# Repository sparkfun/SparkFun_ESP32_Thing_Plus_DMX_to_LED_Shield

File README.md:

SparkFun ESP32 Thing Plus DMX to LED Shield
========================================

[*SparkFun ESP32 DMX to LED Shield(DEV-15110)*](https://www.sparkfun.com/products/15110)

The SparkFun ESP32 DMX to LED Shield is capable of DMX output, input, as well as Artnet input. The shield is electrically isolated to keep with DMX spec. This library has been written to control DMX output and input.

Repository Contents
-------------------

* **/Hardware** - Eagle design files (.brd, .sch)
* **/Production** - Production panel files (.brd)

Documentation
--------------
* **[Hookup Guide](https://learn.sparkfun.com/tutorials/sparkfun-esp32-dmx-to-led-shield)** - Basic hookup guide for the [SparkFun ESP32 DMX to LED Shield](https://www.sparkfun.com/products/15110).

License Information
-------------------

This product is _**open source**_! 

Please review the LICENSE.md file for license information.

If you have any questions or concerns on licensing, please visit the [SparkFun Forum](https://forum.sparkfun.com/index.php) and post a topic.

Distributed as-is; no warranty is given.

- Your friends at SparkFun.

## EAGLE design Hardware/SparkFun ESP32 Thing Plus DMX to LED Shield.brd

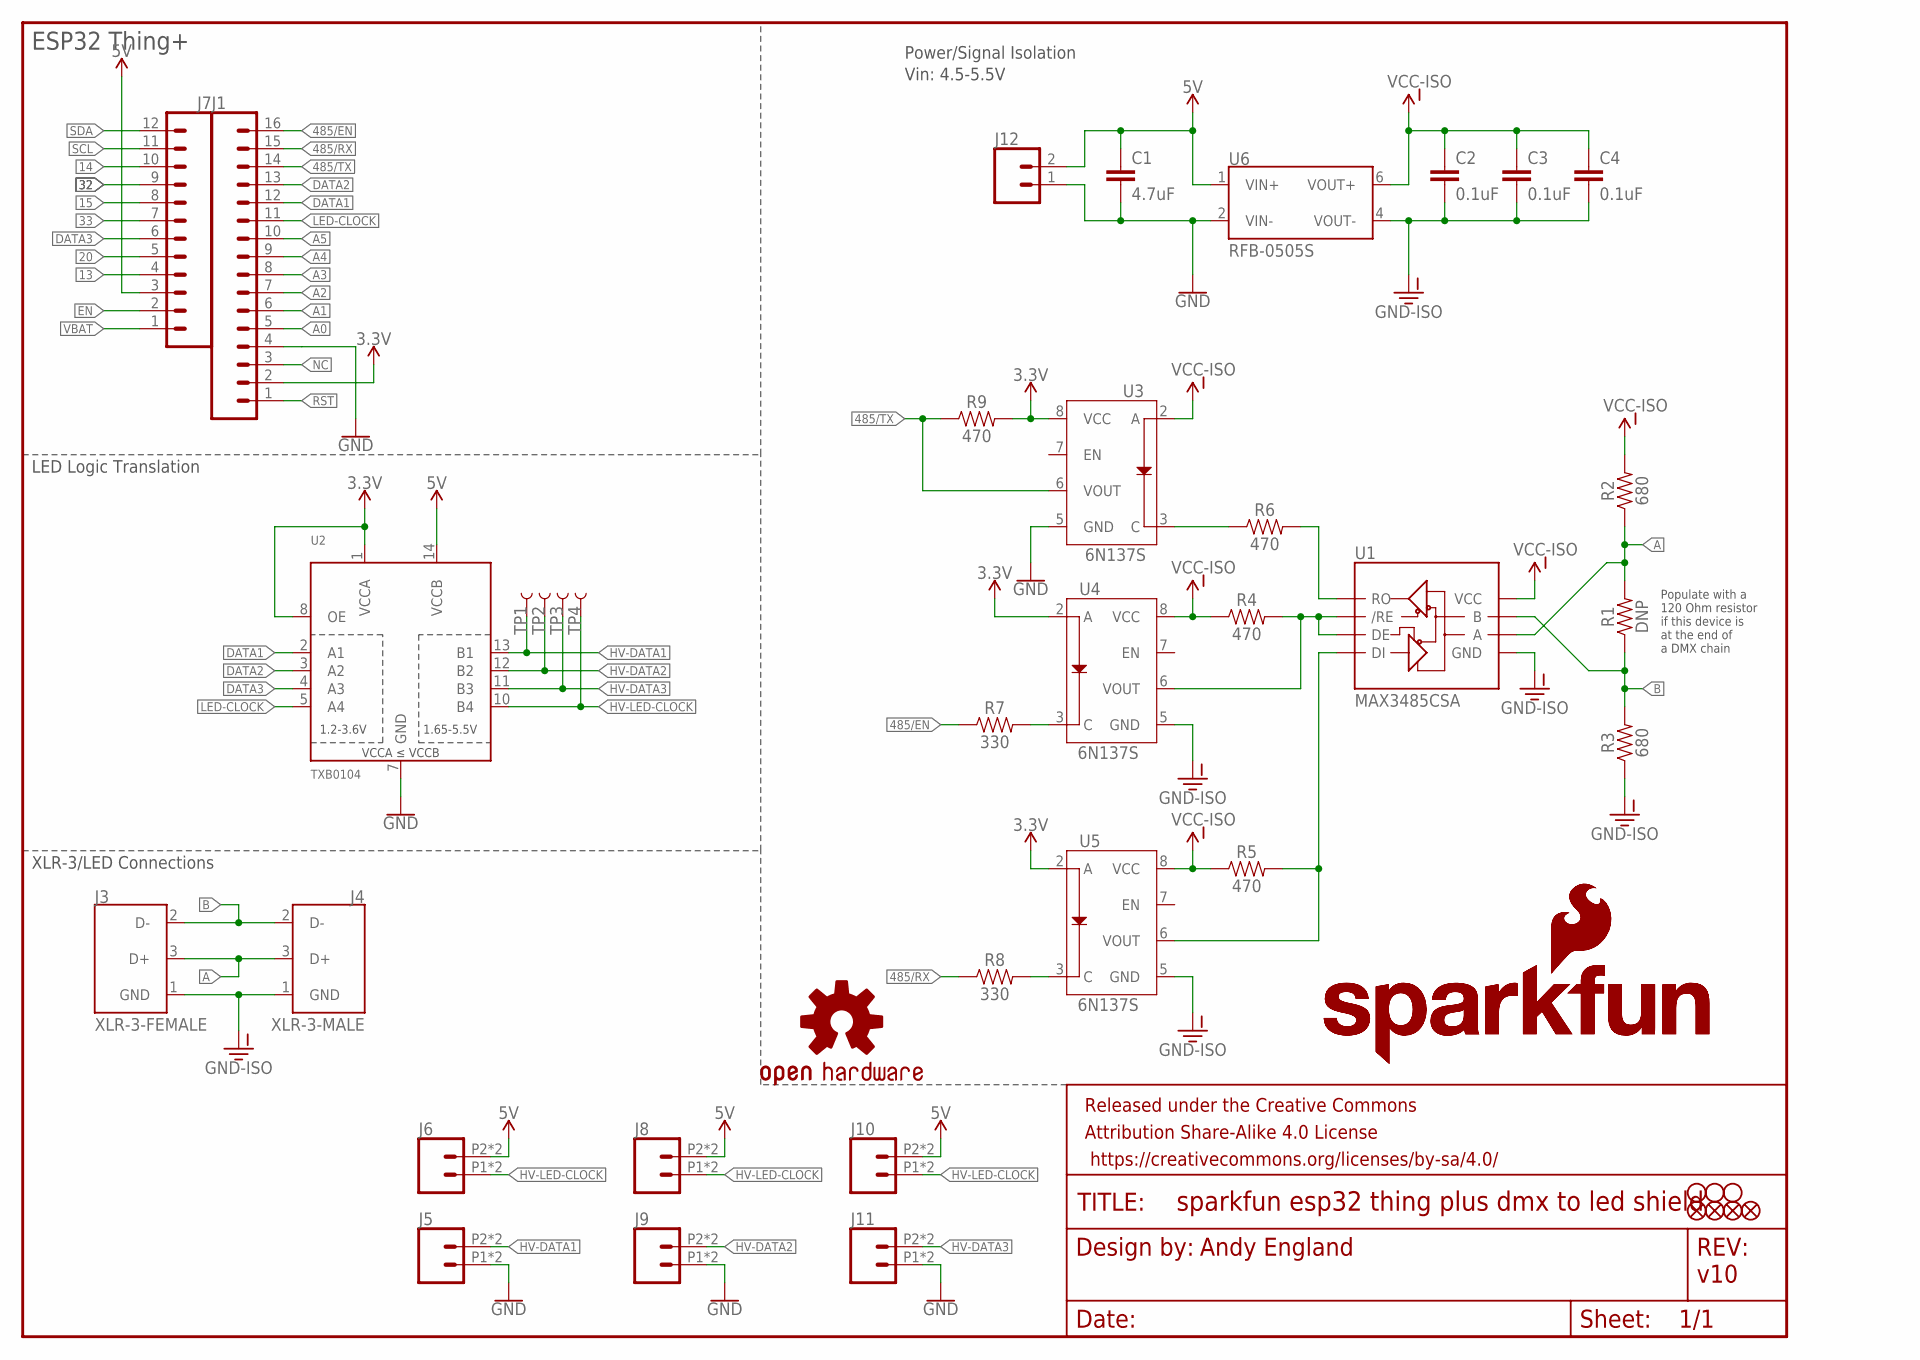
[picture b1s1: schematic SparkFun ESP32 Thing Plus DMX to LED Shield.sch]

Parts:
C1: 4.7uF; 0603
C2, C3, C4: 0.1uF; 0603
FD1, FD2, FD3, FD4: FIDUCIALUFIDUCIAL; FIDUCIAL-MICRO
FRAME1: FRAME-LETTER; CREATIVE_COMMONS
H1, H2, H3: STAND-OFFTIGHT; STAND-OFF-TIGHT
J1: CONN_16LOCK_NO_SILK; 1X16_LOCK_NO_SILK
J3: XLR-3-FEMALE; XLR-3_FEMALE
J4: XLR-3-MALE; XLR-3_MALE
J5, J6, J8, J9, J10, J11: CONN_02SMALL_POKEHOME; 1X02_POKEHOME
J7: CONN_12LOCK_NO_SILK; 1X12_LOCK_NO_SILK
J12: CONN_023.5MM; SCREWTERMINAL-3.5MM-2
LOGO1, LOGO2: SFE_LOGO_NAME_FLAME.2_INCH; SFE_LOGO_NAME_FLAME_.2
LOGO3: OSHW-LOGOS; OSHW-LOGO-S
R1: DNP; AXIAL-0.3EZ
R2, R3: 680; 0603
R4, R5, R6, R9: 470; 0603
R7, R8: 330; 0603
TP1, TP2, TP3, TP4: TEST-POINT3; PAD.03X.03
U1: MAX3485CSA; SO08
U2: TXB0104; TSSOP14
U3, U4, U5: 6N137S; 8-SMD
U6: RFB-0505S

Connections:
3.3V: J1.2, R9.2, U2.1 (VCCA), U2.8 (OE), U3.8 (VCC), U4.2 (A), U5.2 (A)
5V: C1.1, J6.P2 (2), J6.P4 (2), J7.3, J8.P2 (2), J8.P4 (2), J10.P2 (2), J10.P4 (2), J12.2, U2.14 (VCCB), U6.1 (VIN+)
13: J7.4
14: J7.10
15: J7.8
20: J7.5
32: J7.9
33: J7.7
485/EN: J1.16, R7.1
485/RX: J1.15, R8.1
485/TX: J1.14, R9.1, U3.6 (VOUT)
A: J3.3 (D+), J4.3 (D+), R1.P$2 (2), R2.1, U1.6 (A)
A0: J1.5
A1: J1.6
A2: J1.7
A3: J1.8
A4: J1.9
A5: J1.10
B: J3.2 (D-), J4.2 (D-), R1.P$1 (1), R3.2, U1.7 (B)
DATA1: J1.12, U2.2 (A1)
DATA2: J1.13, U2.3 (A2)
DATA3: J7.6, U2.4 (A3)
EN: J7.2
GND: C1.2, J1.4, J5.P1 (1), J5.P3 (1), J9.P1 (1), J9.P3 (1), J11.P1 (1), J11.P3 (1), J12.1, U2.7 (GND), U3.5 (GND), U6.2 (VIN-)
GND-ISO: C2.2, C3.2, C4.2, J3.1 (GND), J4.1 (GND), R3.1, U1.5 (GND), U4.5 (GND), U5.5 (GND), U6.4 (VOUT-)
HV-DATA1: J5.P2 (2), J5.P4 (2), TP1.P$1, U2.13 (B1)
HV-DATA2: J9.P2 (2), J9.P4 (2), TP2.P$1, U2.12 (B2)
HV-DATA3: J11.P2 (2), J11.P4 (2), TP3.P$1, U2.11 (B3)
HV-LED-CLOCK: J6.P1 (1), J6.P3 (1), J8.P1 (1), J8.P3 (1), J10.P1 (1), J10.P3 (1), TP4.P$1, U2.10 (B4)
LED-CLOCK: J1.11, U2.5 (A4)
unnamed: R8.2, U5.3 (C)
unnamed: R7.2, U4.3 (C)
unnamed: R4.2, U1.2 (/RE), U1.3 (DE), U4.6 (VOUT)
unnamed: R5.2, U1.4 (DI), U5.6 (VOUT)
unnamed: R6.1, U3.3 (C)
unnamed: R6.2, U1.1 (RO)
NC: J1.3
RST: J1.1
SCL: J7.11
SDA: J7.12
VBAT: J7.1
VCC-ISO: C2.1, C3.1, C4.1, R2.2, R4.1, R5.1, U1.8 (VCC), U3.2 (A), U4.8 (VCC), U5.8 (VCC), U6.6 (VOUT+)

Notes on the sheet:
ESP32 Thing+
Andy England
v10
LED Logic Translation
Power/Signal Isolation
XLR-3/LED Connections
Populate with a 120 Ohm resistor if this device is at the end of a DMX chain
Vin: 4.5-5.5V

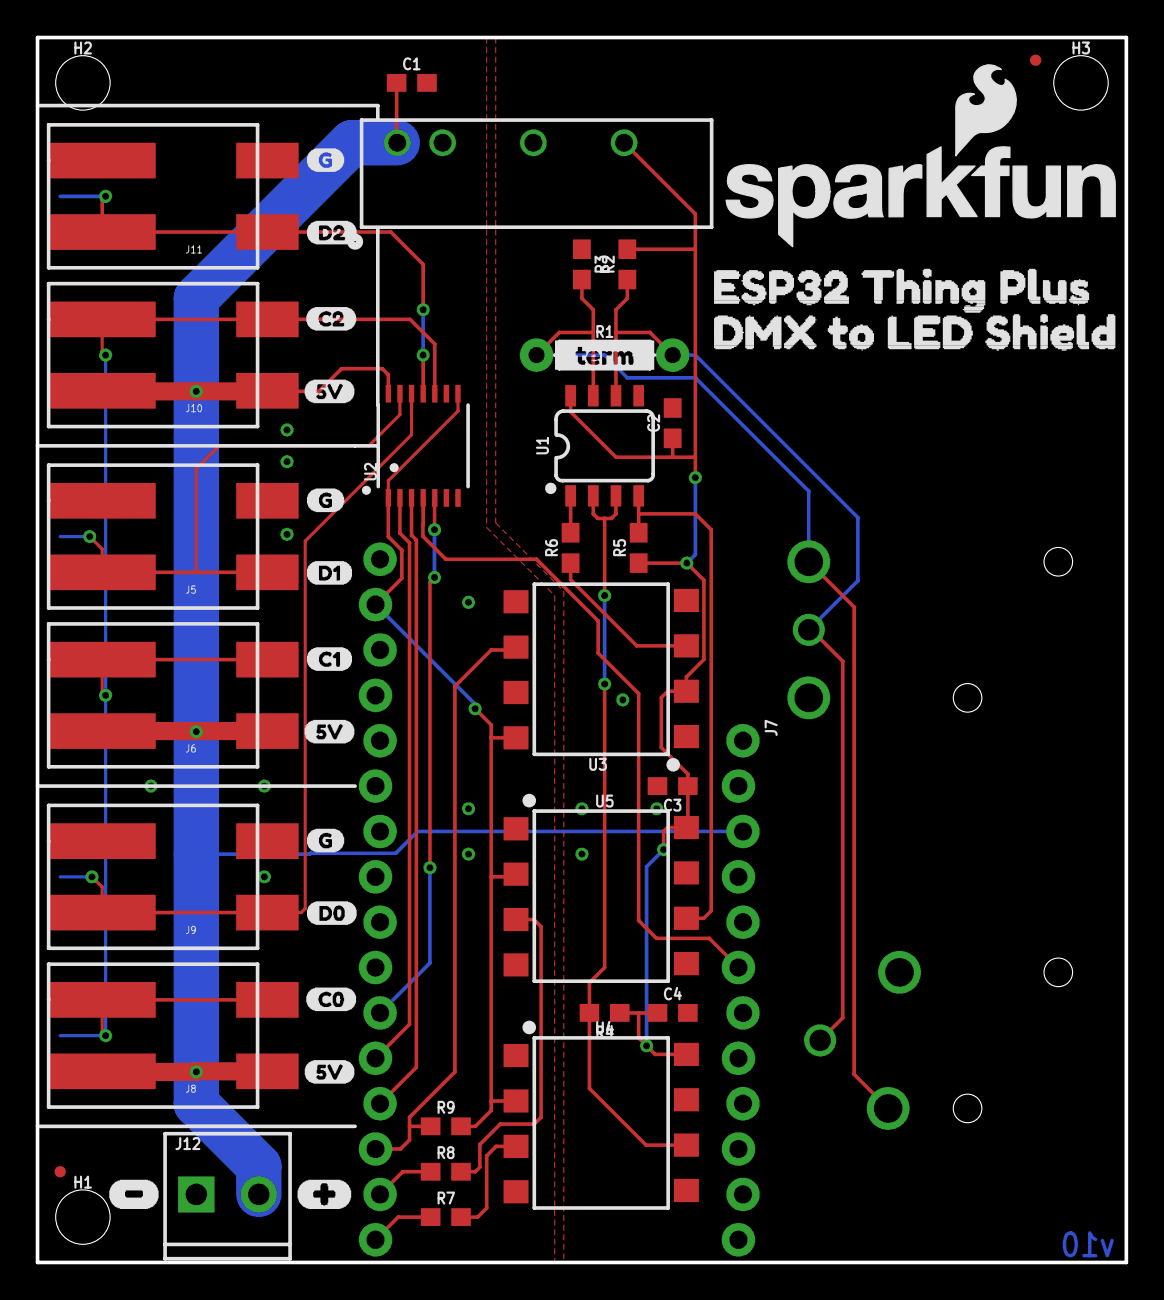
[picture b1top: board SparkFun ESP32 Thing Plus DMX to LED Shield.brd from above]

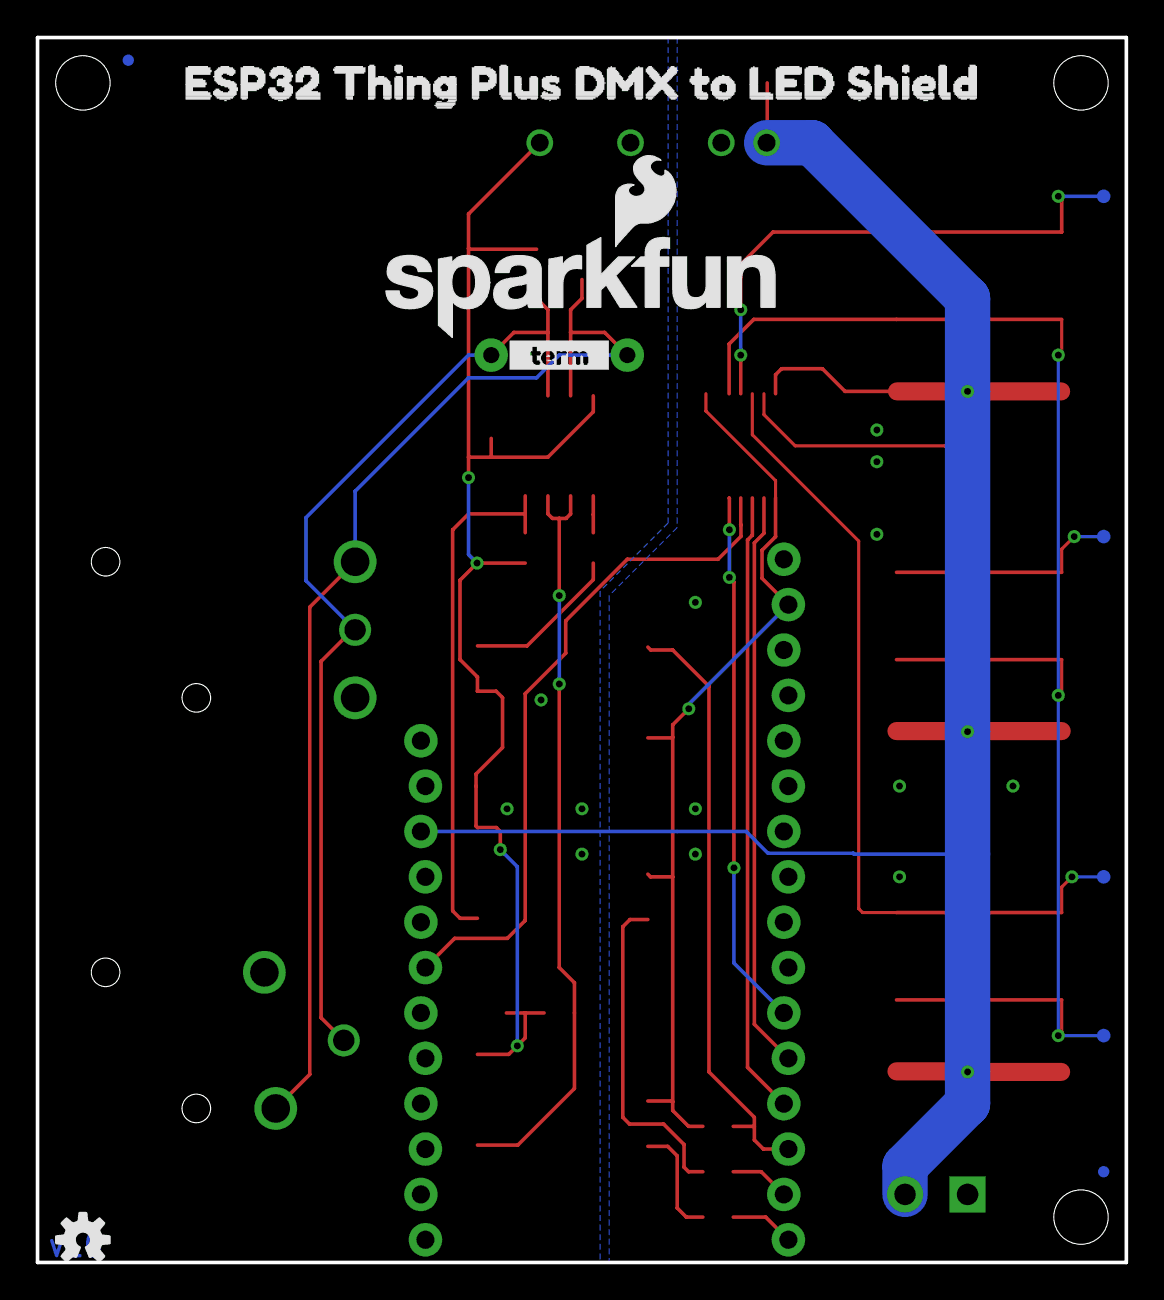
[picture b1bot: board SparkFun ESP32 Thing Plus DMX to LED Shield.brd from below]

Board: 2 copper layers, 61.0 x 68.6 mm, 65 parts (11 on the bottom side), 24 nets.

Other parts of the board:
U$1, U$2: __TERM__0
U$11, U$13: ESP32_THING_PLUS6
U$12, U$14: DMX_TO_LED_SHIELD7
U$15, U$17, U$21: 5V7
U$16: #0
U$18: C01
U$19: D00
U$20, U$24, U$28: G8
U$22: C12
U$23: D16
U$25: #1
U$26: C24
U$27: D23

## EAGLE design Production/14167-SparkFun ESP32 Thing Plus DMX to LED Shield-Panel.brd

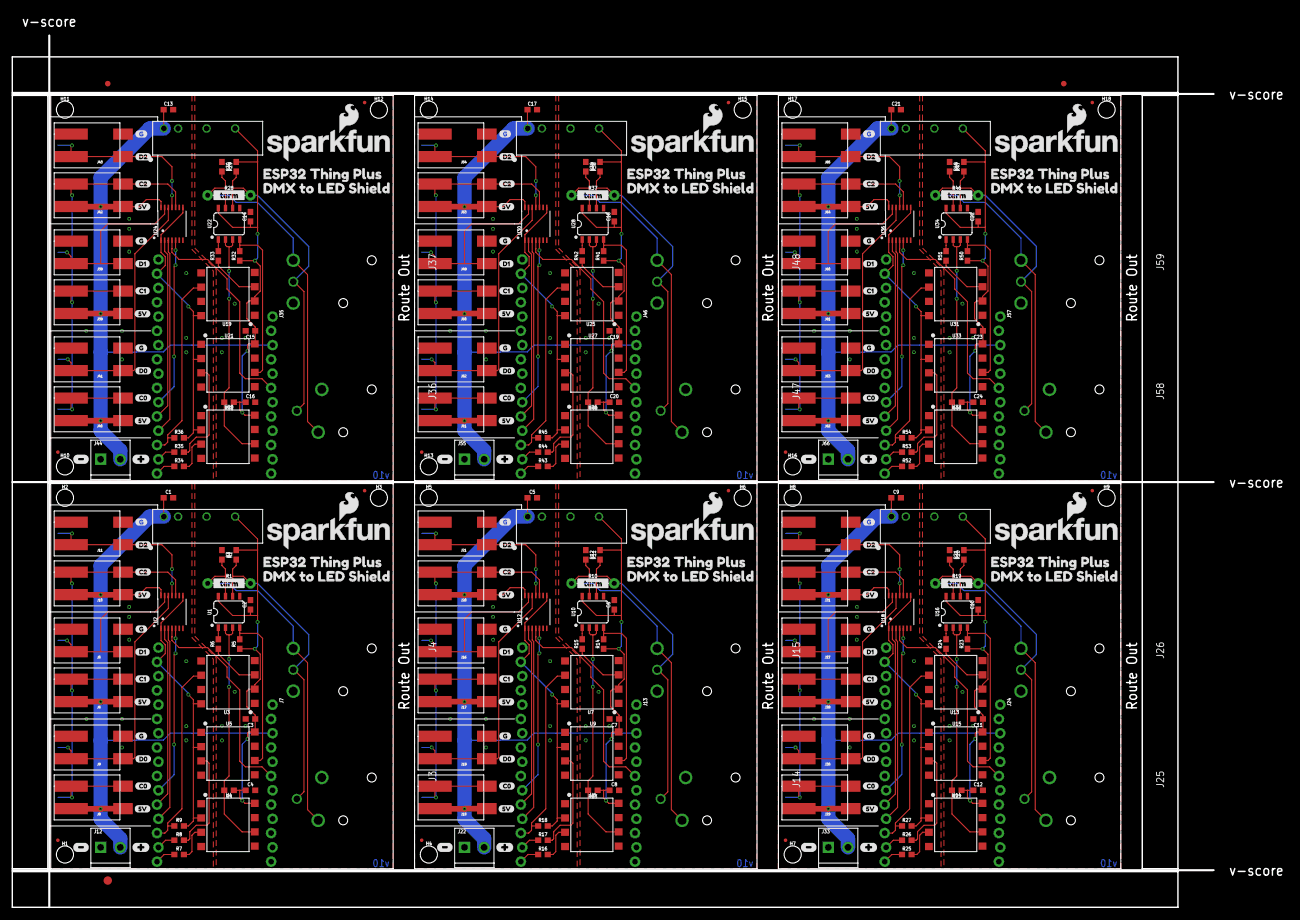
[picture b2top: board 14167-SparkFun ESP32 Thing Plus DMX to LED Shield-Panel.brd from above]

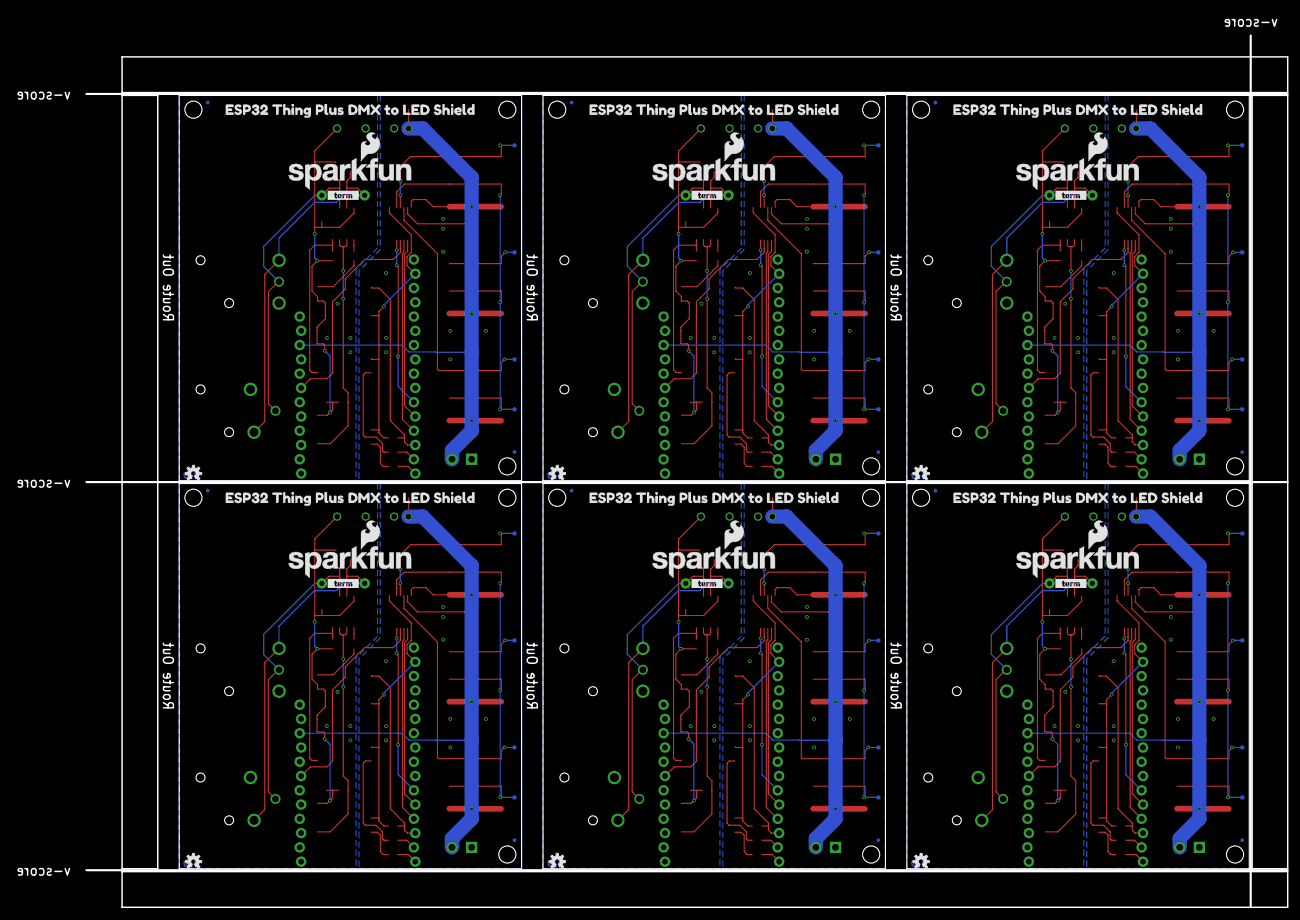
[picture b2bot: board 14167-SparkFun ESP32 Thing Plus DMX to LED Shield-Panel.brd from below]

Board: 2 copper layers, 227.0 x 159.3 mm, 387 parts (66 on the bottom side), 144 nets.

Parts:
C1, C5, C9, C13, C17, C21: 4.7uF; 0603
C2, C3, C4, C6, C7, C8, C10, C11, C12, C14, C15, C16, C18, C19, C20, C22, C23, C24: 0.1uF; 0603
E$1, E$2: FIDUCIAL-1X2
E$3: FIDUCIAL-1.5X3
FD1, FD2, FD3, FD4, FD5, FD6, FD7, FD8, FD9, FD10, FD11, FD12, FD13, FD14, FD15, FD16, FD17, FD18, FD19, FD20, FD21, FD22, FD23, FD24: FIDUCIALUFIDUCIAL; FIDUCIAL-MICRO
H1, H2, H3, H4, H5, H6, H7, H8, H9, H10, H11, H12, H13, H14, H15, H16, H17, H18: STAND-OFFTIGHT; STAND-OFF-TIGHT
J1, J2, J23, J34, J45, J56: 1X16_LOCK_NO_SILK
J3, J14, J25, J36, J47, J58: XLR-3-FEMALE; XLR-3_FEMALE
J4, J15, J26, J37, J48, J59: XLR-3-MALE; XLR-3_MALE
J5, J6, J8, J9, J10, J11, J16, J17, J18, J19, J20, J21, J27, J28, J29, J30, J31, J32, J38, J39, J40, J41, J42, J43, J49, J50, J51, J52, J53, J54, J60, J61, J62, J63, J64, J65: 1X02_POKEHOME
J7, J13, J24, J35, J46, J57: 1X12_LOCK_NO_SILK
J12, J22, J33, J44, J55, J66: SCREWTERMINAL-3.5MM-2
LOGO1, LOGO2, LOGO4, LOGO5, LOGO7, LOGO8, LOGO10, LOGO11, LOGO13, LOGO14, LOGO16, LOGO17: SFE_LOGO_NAME_FLAME.2_INCH; SFE_LOGO_NAME_FLAME_.2
LOGO3, LOGO6, LOGO9, LOGO12, LOGO15, LOGO18: OSHW-LOGOS; OSHW-LOGO-S
R1, R10, R19, R28, R37, R46: DNP; AXIAL-0.3EZ
R2, R3, R11, R12, R20, R21, R29, R30, R38, R39, R47, R48: 680; 0603
R4, R5, R6, R9, R13, R14, R15, R18, R22, R23, R24, R27, R31, R32, R33, R36, R40, R41, R42, R45, R49, R50, R51, R54: 470; 0603
R7, R8, R16, R17, R25, R26, R34, R35, R43, R44, R52, R53: 330; 0603
TP1, TP2, TP3, TP4, TP5, TP6, TP7, TP8, TP9, TP10, TP11, TP12, TP13, TP14, TP15, TP16, TP17, TP18, TP19, TP20, TP21, TP22, TP23, TP24: TEST-POINT3; PAD.03X.03
U1, U10, U16, U22, U28, U34: MAX3485CSA; SO08
U2, U12, U18, U24, U30, U36: TXB0104; TSSOP14
U3, U4, U5, U7, U8, U9, U13, U14, U15, U19, U20, U21, U25, U26, U27, U31, U32, U33: 6N137S; 8-SMD
U6, U11, U17, U23, U29, U35: RFB-0505S
U$1, U$2, U$39, U$40, U$59, U$60, U$79, U$80, U$99, U$100, U$119, U$120: __TERM__0
U$3, U$5, U$11, U$13, U$41, U$43, U$61, U$63, U$81, U$83, U$101, U$103: ESP32_THING_PLUS6
U$4, U$6, U$12, U$14, U$42, U$44, U$62, U$64, U$82, U$84, U$102, U$104: DMX_TO_LED_SHIELD7
U$7, U$8, U$15, U$17, U$21, U$30, U$45, U$46, U$50, U$65, U$66, U$70, U$85, U$86, U$90, U$105, U$106, U$110: 5V7
U$9, U$18, U$47, U$67, U$87, U$107: C01
U$10, U$19, U$48, U$68, U$88, U$108: D00
U$16, U$37, U$57, U$77, U$97, U$117: #0
U$20, U$24, U$28, U$29, U$33, U$36, U$49, U$53, U$56, U$69, U$73, U$76, U$89, U$93, U$96, U$109, U$113, U$116: G8
U$22, U$31, U$51, U$71, U$91, U$111: C12
U$23, U$32, U$52, U$72, U$92, U$112: D16
U$25, U$38, U$58, U$78, U$98, U$118: #1
U$26, U$34, U$54, U$74, U$94, U$114: C24
U$27, U$35, U$55, U$75, U$95, U$115: D23

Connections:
3.3V: J1.2, R9.2, U2.1, U2.8, U3.8, U4.2, U5.2
3.3V1: J2.2, R18.2, U7.8, U8.2, U9.2, U12.1, U12.8
3.3V2: J23.2, R27.2, U13.8, U14.2, U15.2, U18.1, U18.8
3.3V3: J34.2, R36.2, U19.8, U20.2, U21.2, U24.1, U24.8
3.3V4: J45.2, R45.2, U25.8, U26.2, U27.2, U30.1, U30.8
3.3V5: J56.2, R54.2, U31.8, U32.2, U33.2, U36.1, U36.8
5V: C1.1, J6.P2, J6.P4, J7.3, J8.P2, J8.P4, J10.P2, J10.P4, J12.2, U2.14, U6.1
5V1: C5.1, J13.3, J17.P2, J17.P4, J18.P2, J18.P4, J20.P2, J20.P4, J22.2, U11.1, U12.14
5V2: C9.1, J24.3, J28.P2, J28.P4, J29.P2, J29.P4, J31.P2, J31.P4, J33.2, U17.1, U18.14
5V3: C13.1, J35.3, J39.P2, J39.P4, J40.P2, J40.P4, J42.P2, J42.P4, J44.2, U23.1, U24.14
5V4: C17.1, J46.3, J50.P2, J50.P4, J51.P2, J51.P4, J53.P2, J53.P4, J55.2, U29.1, U30.14
5V5: C21.1, J57.3, J61.P2, J61.P4, J62.P2, J62.P4, J64.P2, J64.P4, J66.2, U35.1, U36.14
485/EN: J1.16, R7.1
485/EN1: J2.16, R16.1
485/EN2: J23.16, R25.1
485/EN3: J34.16, R34.1
485/EN4: J45.16, R43.1
485/EN5: J56.16, R52.1
485/RX: J1.15, R8.1
485/RX1: J2.15, R17.1
485/RX2: J23.15, R26.1
485/RX3: J34.15, R35.1
485/RX4: J45.15, R44.1
485/RX5: J56.15, R53.1
485/TX: J1.14, R9.1, U3.6
485/TX1: J2.14, R18.1, U7.6
485/TX2: J23.14, R27.1, U13.6
485/TX3: J34.14, R36.1, U19.6
485/TX4: J45.14, R45.1, U25.6
485/TX5: J56.14, R54.1, U31.6
A: J3.3, J4.3, R1.P$2, R2.1, U1.6
A12: J14.3, J15.3, R10.P$2, R11.1, U10.6
A19: J25.3, J26.3, R19.P$2, R20.1, U16.6
A26: J36.3, J37.3, R28.P$2, R29.1, U22.6
A33: J47.3, J48.3, R37.P$2, R38.1, U28.6
A40: J58.3, J59.3, R46.P$2, R47.1, U34.6
B: J3.2, J4.2, R1.P$1, R3.2, U1.7
B1: J14.2, J15.2, R10.P$1, R12.2, U10.7
B2: J25.2, J26.2, R19.P$1, R21.2, U16.7
B3: J36.2, J37.2, R28.P$1, R30.2, U22.7
B4: J47.2, J48.2, R37.P$1, R39.2, U28.7
B5: J58.2, J59.2, R46.P$1, R48.2, U34.7
DATA1: J1.12, U2.2
DATA2: J1.13, U2.3
DATA3: J7.6, U2.4
DATA4: J13.6, U12.4
DATA5: J2.13, U12.3
DATA6: J2.12, U12.2
DATA7: J24.6, U18.4
DATA8: J23.13, U18.3
DATA9: J23.12, U18.2
DATA10: J35.6, U24.4
DATA11: J34.13, U24.3
DATA12: J34.12, U24.2
DATA13: J46.6, U30.4
DATA14: J45.13, U30.3
DATA15: J45.12, U30.2
DATA16: J57.6, U36.4
DATA17: J56.13, U36.3
DATA18: J56.12, U36.2
GND: C1.2, J1.4, J5.P1, J5.P3, J9.P1, J9.P3, J11.P1, J11.P3, J12.1, U2.7, U3.5, U6.2
GND1: C5.2, J2.4, J16.P1, J16.P3, J19.P1, J19.P3, J21.P1, J21.P3, J22.1, U7.5, U11.2, U12.7
GND2: C9.2, J23.4, J27.P1, J27.P3, J30.P1, J30.P3, J32.P1, J32.P3, J33.1, U13.5, U17.2, U18.7
GND3: C13.2, J34.4, J38.P1, J38.P3, J41.P1, J41.P3, J43.P1, J43.P3, J44.1, U19.5, U23.2, U24.7
GND4: C17.2, J45.4, J49.P1, J49.P3, J52.P1, J52.P3, J54.P1, J54.P3, J55.1, U25.5, U29.2, U30.7
GND5: C21.2, J56.4, J60.P1, J60.P3, J63.P1, J63.P3, J65.P1, J65.P3, J66.1, U31.5, U35.2, U36.7
GND-ISO: C2.2, C3.2, C4.2, J3.1, J4.1, R3.1, U1.5, U4.5, U5.5, U6.4
GND-ISO1: C6.2, C7.2, C8.2, J14.1, J15.1, R12.1, U8.5, U9.5, U10.5, U11.4
GND-ISO2: C10.2, C11.2, C12.2, J25.1, J26.1, R21.1, U14.5, U15.5, U16.5, U17.4
GND-ISO3: C14.2, C15.2, C16.2, J36.1, J37.1, R30.1, U20.5, U21.5, U22.5, U23.4
GND-ISO4: C18.2, C19.2, C20.2, J47.1, J48.1, R39.1, U26.5, U27.5, U28.5, U29.4
GND-ISO5: C22.2, C23.2, C24.2, J58.1, J59.1, R48.1, U32.5, U33.5, U34.5, U35.4
HV-DATA1: J5.P2, J5.P4, TP1.P$1, U2.13
HV-DATA2: J9.P2, J9.P4, TP2.P$1, U2.12
HV-DATA3: J11.P2, J11.P4, TP3.P$1, U2.11
HV-DATA4: J19.P2, J19.P4, TP6.P$1, U12.12
HV-DATA5: J21.P2, J21.P4, TP7.P$1, U12.11
HV-DATA6: J16.P2, J16.P4, TP5.P$1, U12.13
HV-DATA7: J30.P2, J30.P4, TP10.P$1, U18.12
HV-DATA8: J32.P2, J32.P4, TP11.P$1, U18.11
HV-DATA9: J27.P2, J27.P4, TP9.P$1, U18.13
HV-DATA10: J41.P2, J41.P4, TP14.P$1, U24.12
HV-DATA11: J43.P2, J43.P4, TP15.P$1, U24.11
HV-DATA12: J38.P2, J38.P4, TP13.P$1, U24.13
HV-DATA13: J52.P2, J52.P4, TP18.P$1, U30.12
HV-DATA14: J54.P2, J54.P4, TP19.P$1, U30.11
HV-DATA15: J49.P2, J49.P4, TP17.P$1, U30.13
HV-DATA16: J63.P2, J63.P4, TP22.P$1, U36.12
HV-DATA17: J65.P2, J65.P4, TP23.P$1, U36.11
HV-DATA18: J60.P2, J60.P4, TP21.P$1, U36.13
HV-LED-CLOCK: J6.P1, J6.P3, J8.P1, J8.P3, J10.P1, J10.P3, TP4.P$1, U2.10
HV-LED-CLOCK1: J17.P1, J17.P3, J18.P1, J18.P3, J20.P1, J20.P3, TP8.P$1, U12.10
HV-LED-CLOCK2: J28.P1, J28.P3, J29.P1, J29.P3, J31.P1, J31.P3, TP12.P$1, U18.10
HV-LED-CLOCK3: J39.P1, J39.P3, J40.P1, J40.P3, J42.P1, J42.P3, TP16.P$1, U24.10
HV-LED-CLOCK4: J50.P1, J50.P3, J51.P1, J51.P3, J53.P1, J53.P3, TP20.P$1, U30.10
HV-LED-CLOCK5: J61.P1, J61.P3, J62.P1, J62.P3, J64.P1, J64.P3, TP24.P$1, U36.10
LED-CLOCK: J1.11, U2.5
LED-CLOCK1: J2.11, U12.5
LED-CLOCK2: J23.11, U18.5
LED-CLOCK3: J34.11, U24.5
LED-CLOCK4: J45.11, U30.5
LED-CLOCK5: J56.11, U36.5
unnamed: R8.2, U5.3
unnamed: R7.2, U4.3
unnamed: R4.2, U1.2, U1.3, U4.6
unnamed: R5.2, U1.4, U5.6
unnamed: R6.1, U3.3
unnamed: R6.2, U1.1
unnamed: R13.2, U8.6, U10.2, U10.3
unnamed: R15.1, U7.3
unnamed: R15.2, U10.1
unnamed: R14.2, U9.6, U10.4
unnamed: R17.2, U9.3
unnamed: R16.2, U8.3
unnamed: R22.2, U14.6, U16.2, U16.3
unnamed: R24.1, U13.3
unnamed: R24.2, U16.1
unnamed: R23.2, U15.6, U16.4
unnamed: R26.2, U15.3
unnamed: R25.2, U14.3
unnamed: R31.2, U20.6, U22.2, U22.3
unnamed: R33.1, U19.3
unnamed: R33.2, U22.1
unnamed: R32.2, U21.6, U22.4
unnamed: R35.2, U21.3
unnamed: R34.2, U20.3
unnamed: R40.2, U26.6, U28.2, U28.3
unnamed: R42.1, U25.3
unnamed: R42.2, U28.1
unnamed: R41.2, U27.6, U28.4
unnamed: R44.2, U27.3
unnamed: R43.2, U26.3
unnamed: R49.2, U32.6, U34.2, U34.3
unnamed: R51.1, U31.3
unnamed: R51.2, U34.1
unnamed: R50.2, U33.6, U34.4
unnamed: R53.2, U33.3
unnamed: R52.2, U32.3
VCC-ISO: C2.1, C3.1, C4.1, R2.2, R4.1, R5.1, U1.8, U3.2, U4.8, U5.8, U6.6
VCC-ISO1: C6.1, C7.1, C8.1, R11.2, R13.1, R14.1, U7.2, U8.8, U9.8, U10.8, U11.6
VCC-ISO2: C10.1, C11.1, C12.1, R20.2, R22.1, R23.1, U13.2, U14.8, U15.8, U16.8, U17.6
VCC-ISO3: C14.1, C15.1, C16.1, R29.2, R31.1, R32.1, U19.2, U20.8, U21.8, U22.8, U23.6
VCC-ISO4: C18.1, C19.1, C20.1, R38.2, R40.1, R41.1, U25.2, U26.8, U27.8, U28.8, U29.6
VCC-ISO5: C22.1, C23.1, C24.1, R47.2, R49.1, R50.1, U31.2, U32.8, U33.8, U34.8, U35.6

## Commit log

2018-11-21 post review changes
2018-11-26 QC changes
2019-01-18 adding beginning of example code
2019-02-13 adding all examples
2019-02-15 updating for reds
2019-02-19 post checklist changes
2019-02-19 a few unsaved changes
2019-02-19 changing name, post checklist changes
2019-02-20 Created panel v10
2019-03-28 updating readme
2019-03-28 Update README.md
    No Fritzing Diagram or Graphical Datasheet.
    Corrected product name in hookup guide link.
2019-05-24 Remove TS email address
2019-05-24 Added link to forums for licensing

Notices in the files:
parts and their libraries:
SparkFun-Aesthetics: Licensing: Creative Commons ShareAlike 4.0 International - https://creativecommons.org/licenses/by-sa/4.0
SparkFun-Aesthetics: Released under the Creative Commons Attribution Share-Alike 4.0 License
SparkFun-Aesthetics: https://creativecommons.org/licenses/by-sa/4.0
